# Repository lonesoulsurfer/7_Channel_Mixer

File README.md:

YouTube - https://youtu.be/h-TxdCl6BcE

Instructables - https://www.instructables.com/7-Channel-Mixer-a-4-Channel-Option/

Here you can find everything you need to make your own 7 Channel Mixer.  This is based on Syntherjacks awesome little 4sum mixer which you can find a link below to.  My modular synth runs off 9/5V so this amp works perfectly for what I need.  You could also power it via traditional Eurorack style powering, you would just have to add a step down converter from the mixer to the 12V power source.

I have also included a Eurorack 4 channel version as well which will fit perfectly into any Eurorack.

https://syntherjack.net/portable-audio-mixer/

7 Channel Mixer - Circuit Explanation

This is a passive-input, op-amp buffered audio mixer built around an NE5532N dual op-amp. 

Here's how it works from input to output:

Input Stage (7 Channels)

* Each of the 7 channels (IN_1 through IN_7) follows the same structure. A 3-pin connector feeds into a 100K potentiometer (VOL_1 through VOL_7) which acts as the individual channel volume control. The wiper of each pot    connects through a 47K resistor to a common summing node. The 47K resistors serve as summing/isolation resistors — they prevent channels from loading each other and set the gain relationship between channels.

Summing & First Op-Amp Stage (IC1A)

* All 7 channel signals meet at the summing node, which connects through a 10µF coupling capacitor (blocking any DC offset) into the non-inverting (+) input of IC1A (the first half of the NE5532N). IC1A is configured as a unity-gain buffer with a 47K feedback resistor, providing a low-impedance version of the mixed signal. VREF is applied to bias the op-amp at the virtual mid-rail since this is a single-supply design.

Second Op-Amp Stage (IC1B) + Master Level

* The output of IC1A feeds into IC1B (the second half of the NE5532N). A 100K master LEVEL potentiometer in the feedback path of IC1B controls the overall output gain/volume. This gives you master level control over the entire mix.

Output Stage

* The output of IC1B passes through another 10µF coupling capacitor (again blocking DC) into an output volume pot and then to the OUT_1 connector.

Power Supply

* The circuit runs off a single +9V supply (PWR_9V connector). A BAT43 Schottky diode provides reverse polarity protection. Two 100µF filter capacitors smooth the supply rail. A resistor divider made of two 47K resistors creates a VREF mid-rail reference (~4.5V), which biases the op-amp stages so they can handle AC audio signals on a single supply. A LED with current-limiting resistor provides a power indicator.

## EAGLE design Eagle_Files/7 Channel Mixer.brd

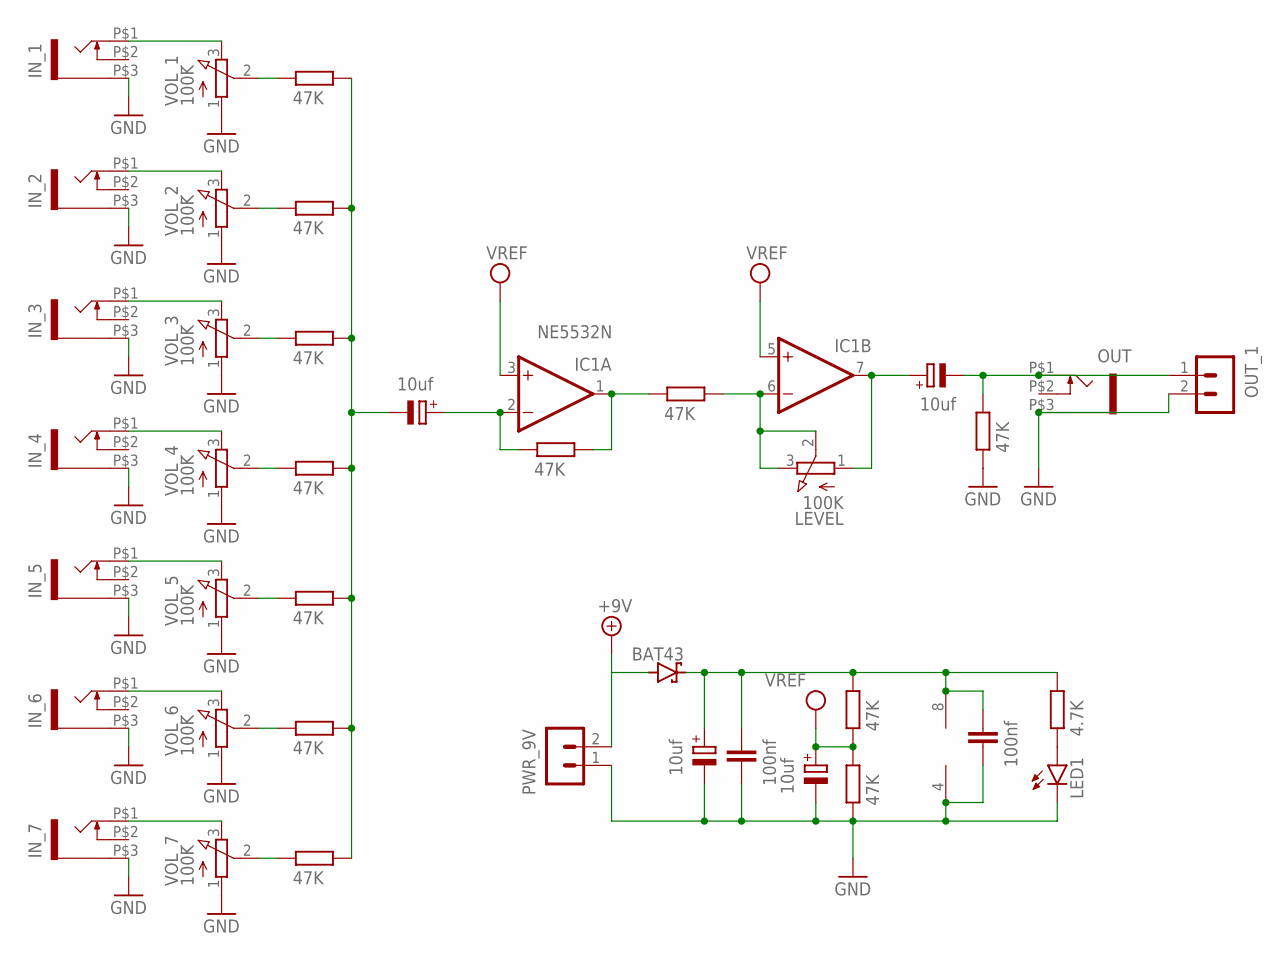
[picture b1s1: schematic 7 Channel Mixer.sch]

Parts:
C1, C2, C3, C4: 10uf; E2,5-6E
C5, C6: 100nf; C050-024X044
D4: BAT43; DO35-10
IC1: NE5532N; DIL08
IN_1, IN_2, IN_3, IN_4, IN_5, IN_6, IN_7: WQP-PJ301M-12_JACK
LED1: LED3MM
LEVEL: 100K; EVUFXM
OUT: WQP-PJ301M-12_JACK
OUT_1: B2B-PH-K-S
PWR_9V: B2B-PH-K-S
R1, R2, R3, R4, R5, R6, R7, R8, R9, R10, R11, R13: 47K; 0204/7
R12: 4.7K; 0204/7
VOL_1, VOL_2, VOL_3, VOL_4, VOL_5, VOL_6, VOL_7: 100K; EVUFXM

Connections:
+9V: D4.A, PWR_9V.2
GND: C3.-, C4.-, C5.1, C6.1, IC1.4 (V-), IN_1.P$3 (1), IN_2.P$3 (1), IN_3.P$3 (1), IN_4.P$3 (1), IN_5.P$3 (1), IN_6.P$3 (1), IN_7.P$3 (1), LED1.K (C), OUT.P$3 (1), OUT_1.2, PWR_9V.1, R9.2, R11.2, VOL_1.1 (A), VOL_2.1 (A), VOL_3.1 (A), VOL_4.1 (A), VOL_5.1 (A), VOL_6.1 (A), VOL_7.1 (A)
unnamed: IN_7.P$1 (2), VOL_7.3 (E)
unnamed: R1.2, VOL_2.2 (S)
unnamed: IN_5.P$1 (2), VOL_5.3 (E)
unnamed: R2.2, VOL_3.2 (S)
unnamed: IN_6.P$1 (2), VOL_6.3 (E)
unnamed: R3.2, VOL_4.2 (S)
unnamed: IN_3.P$1 (2), VOL_3.3 (E)
unnamed: R5.2, VOL_1.2 (S)
unnamed: R4.2, VOL_5.2 (S)
unnamed: IN_4.P$1 (2), VOL_4.3 (E)
unnamed: R6.2, VOL_6.2 (S)
unnamed: C1.-, R1.1, R2.1, R3.1, R4.1, R5.1, R6.1, R13.1
unnamed: C2.-, OUT.P$1 (2), OUT_1.1, R9.1
unnamed: C1.+, IC1.2 (-IN), R7.2
unnamed: IN_2.P$1 (2), VOL_2.3 (E)
unnamed: IC1.1 (OUT), R7.1, R8.2
unnamed: IC1.6 (-IN), LEVEL.2 (S), LEVEL.3 (E), R8.1
unnamed: C2.+, IC1.7 (OUT), LEVEL.1 (A)
unnamed: LED1.A, R12.2
unnamed: C4.+, C5.2, C6.2, D4.C, IC1.8 (V+), R10.1, R12.1
unnamed: IN_1.P$1 (2), VOL_1.3 (E)
unnamed: R13.2, VOL_7.2 (S)
VCC: C3.+, IC1.3 (+IN), IC1.5 (+IN), R10.2, R11.1

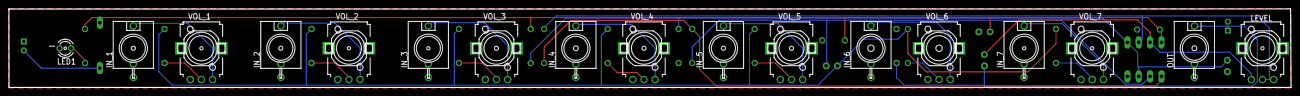
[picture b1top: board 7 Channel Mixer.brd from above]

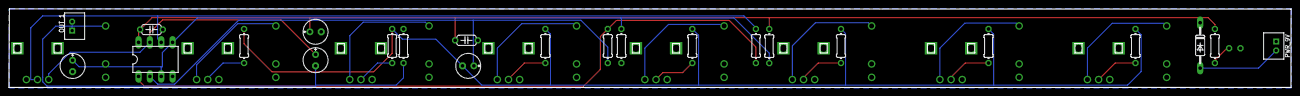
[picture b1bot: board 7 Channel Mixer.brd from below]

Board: 2 copper layers, 287.0 x 17.6 mm, 40 parts (23 on the bottom side), 25 nets.

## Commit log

2026-02-21 Add circuit explanation for 7 Channel Mixer
    Added detailed explanation of the 7 Channel Mixer circuit, including input stages, op-amp configurations, and power supply details.
2026-02-21 Update README.md for improved clarity and formatting
    Corrected formatting and added missing sections for clarity.
2026-02-21 Format input stage and circuit description with bullet points
    Updated README.md to use bullet points for clarity.
2026-02-21 Fix typos in README.md
    Corrected typos in the README regarding the 7 Channel Mixer.
2026-02-21 Update README with images and TBA sections
    Added images and placeholders for video and Instructables sections.
